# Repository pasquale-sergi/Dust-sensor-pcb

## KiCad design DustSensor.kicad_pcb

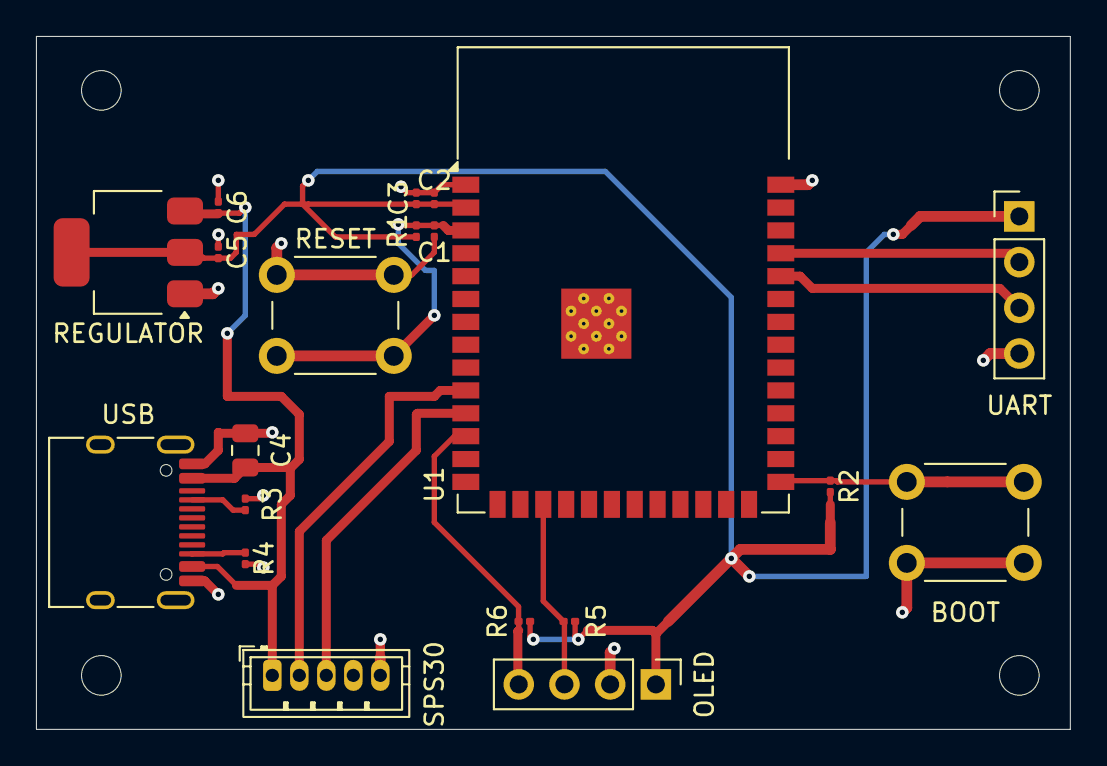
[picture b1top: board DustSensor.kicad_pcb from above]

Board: 2 copper layers, 57.4 x 38.5 mm, 21 parts (0 on the bottom side), 13 nets.

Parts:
BOOT: BOOT; SW_PUSH_6mm_H5mm
C1: 1uF; C_0201_0603Metric
C2, C5: 22uF; C_0201_0603Metric
C3: 0.1uF; C_0201_0603Metric
C4: 22uF; C_0805_2012Metric
C6: 10uF; C_0201_0603Metric
OLED: OLED_CONN; PinHeader_1x04_P2.54mm_Vertical
R1, R2: 10k; R_0201_0603Metric
R3, R4: 5.1k; R_0201_0603Metric
R5, R6: 4.7k; R_0201_0603Metric
REF: MountingHole_2.2mm_M2
REGULATOR: AMS1117-3.3; SOT-223-3_TabPin2
RESET: RESET; SW_PUSH_6mm_H5mm
SPS30: SPS30_CONN; JST_ZH_B5B-ZR_1x05_P1.50mm_Vertical
U1: ESP32-S3-WROOM-1
UART: UART_CONNECTOR; PinHeader_1x04_P2.54mm_Vertical
USB: USB_C_CONN; USB_C_Receptacle_HRO_TYPE-C-31-M-12

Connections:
/3v3: C2.1, C3.2, C5.2, OLED.1, R1.1, R2.2, R5.1, R6.1, REGULATOR.2 (VO), U1.2 (3V3), UART.1
/5V: C4.1, C6.2, REGULATOR.3 (VI), SPS30.1, USB.A4 (VBUS), USB.A9 (VBUS), USB.B4 (VBUS), USB.B9 (VBUS)
/OLED_SCL: OLED.3, R5.2, U1.17 (IO9)
/OLED_SDA: OLED.4, R6.2, U1.12 (IO8)
/SPS30RX: SPS30.2, U1.10 (IO17)
/SPS30TX: SPS30.3, U1.11 (IO18)
/UART_RX: U1.37 (TXD0), UART.2
/UART_TX: U1.36 (RXD0), UART.3
GND: BOOT.1, C1.1, C2.2, C3.1, C4.2, C5.1, C6.1, OLED.2, R3.2, R4.2, REGULATOR.1 (GND), RESET.1, SPS30.5, U1.1 (GND), U1.40 (GND), U1.41 (GND), UART.4, USB.A1 (GND), USB.A12 (GND), USB.B1 (GND), USB.B12 (GND)
unnamed: R3.1, USB.A5 (CC1)
unnamed: R4.1, USB.B5 (CC2)
unnamed: C1.2, R1.2, RESET.2, U1.3 (EN)
unnamed: BOOT.2, R2.1, U1.27 (IO0)

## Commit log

2026-04-23 schematic done and started layout
2026-04-24 Started routing
